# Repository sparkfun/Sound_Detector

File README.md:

#Sound_detector
***

[  
*Sound Detector*](https://www.sparkfun.com/products/12642)  

Electret microphone with multiple outputs.

* First output is the actual audio
* Second output is the amplitude envelope
* Third output is a binary "sound present" indication - high while sound is present, low otherwise.

Design and firmware files for the [VKey Voltage Keypad](https://www.sparkfun.com/products/12080).

Repository Contents
-------------------

* **/Documents** - Additional design files including LTspice simulation  
* **/Hardware** - Eagle PCB and schematic files
* **/Production** - Production panel file
* **/Software** - Arduino example code

License Information
-------------------
The hardware is released under [Creative Commons ShareAlike 4.0 International](https://creativecommons.org/licenses/by-sa/4.0/).
The code is beerware; if you see me (or any other SparkFun employee) at the local, and you've found our code helpful, please buy us a round!

Distributed as-is; no warranty is given.

Author: Byron Jacquot @ SparkFun Electonics

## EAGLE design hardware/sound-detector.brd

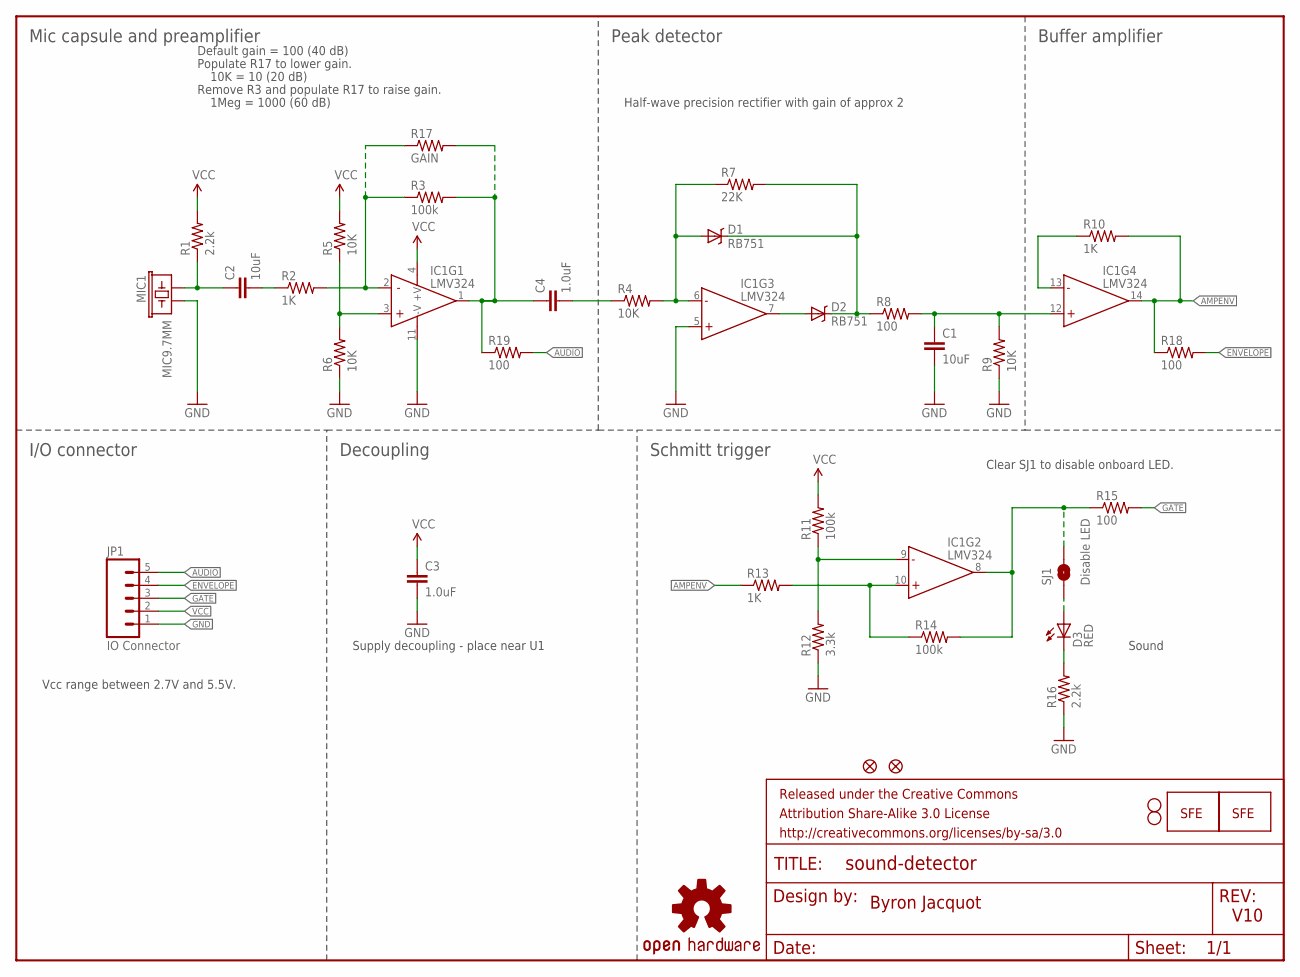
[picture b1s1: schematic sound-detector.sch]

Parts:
C1, C2: 10uF; 1206
C3, C4: 1.0uF; 0603-CAP
D1, D2: RB751; SOD-523
D3: RED; LED-0603
FID3, FID4: FIDUCIAL1X2; FIDUCIAL-1X2
FRAME1: FRAME-LETTER; CREATIVE_COMMONS
IC1: LMV324; SO014
JP1: IO Connector; 1X05
LOGO1: OSHW-LOGOM; OSHW-LOGO-M
LOGO2: LOGO-SFENW2; SFE-NEW-WEB
LOGO3: LOGO-SFESK; SFE-LOGO-FLAME
MIC1: MIC9.7MM; MIC-9.7MM
R1, R16: 2.2k; 0603-RES
R2, R10, R13: 1K; 0603-RES
R3, R11, R14: 100k; 0603-RES
R4, R5, R6, R9: 10K; 0603-RES
R7: 22K; 0603-RES
R8, R15, R18, R19: 100; 0603-RES
R12: 3.3k; 0603-RES
R17: GAIN; AXIAL-0.1EZ
SJ1: Disable LED; SJ_2S
STANDOFF1, STANDOFF2: STAND-OFF

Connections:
AMPENV: IC1.14 (OUT), R10.2, R13.1, R18.1
AUDIO: JP1.5, R19.2
ENVELOPE: JP1.4, R18.2
GATE: JP1.3, R15.2
GND: C1.2, C3.2, IC1.5 (+IN), IC1.11 (-V), JP1.1, MIC1.2, R6.1, R9.1, R12.1, R16.1
N$: C4.1, IC1.1 (OUT), R3.2, R17.P$2 (2), R19.1
unnamed: C2.1, MIC1.1, R1.1
unnamed: IC1.3 (+IN), R5.1, R6.2
unnamed: D3.C, R16.2
unnamed: IC1.2 (-IN), R2.2, R3.1, R17.P$1 (1)
unnamed: C2.2, R2.1
unnamed: C4.2, R4.1
unnamed: D1.A, IC1.6 (-IN), R4.2, R7.1
unnamed: D2.A, IC1.7 (OUT)
unnamed: D1.C, D2.C, R7.2, R8.1
unnamed: C1.1, IC1.12 (+IN), R8.2, R9.2
unnamed: IC1.13 (-IN), R10.1
unnamed: D3.A, SJ1.1
unnamed: IC1.9 (-IN), R11.1, R12.2
unnamed: IC1.10 (+IN), R13.2, R14.1
unnamed: IC1.8 (OUT), R14.2, R15.1, SJ1.2
VCC: C3.1, IC1.4 (+V), JP1.2, R1.2, R5.2, R11.2

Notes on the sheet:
Byron Jacquot
V10
Supply decoupling - place near U1
Mic capsule and preamplifier
Peak detector
Buffer amplifier
I/O connector
Decoupling
Schmitt trigger
Default gain = 100 (40 dB)
Half-wave precision rectifier with gain of approx 2
Vcc range between 2.7V and 5.5V.
Sound
Populate R17 to lower gain.
10K = 10 (20 dB)
Remove R3 and populate R17 to raise gain.
1Meg = 1000 (60 dB)
Clear SJ1 to disable onboard LED.

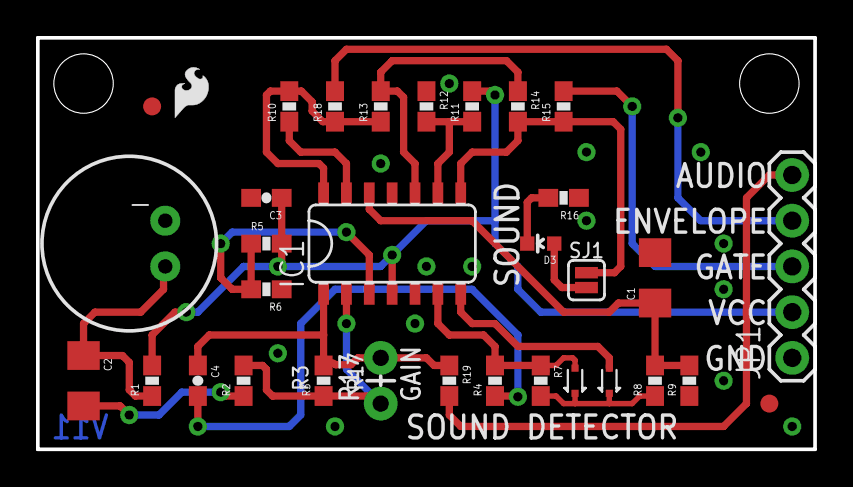
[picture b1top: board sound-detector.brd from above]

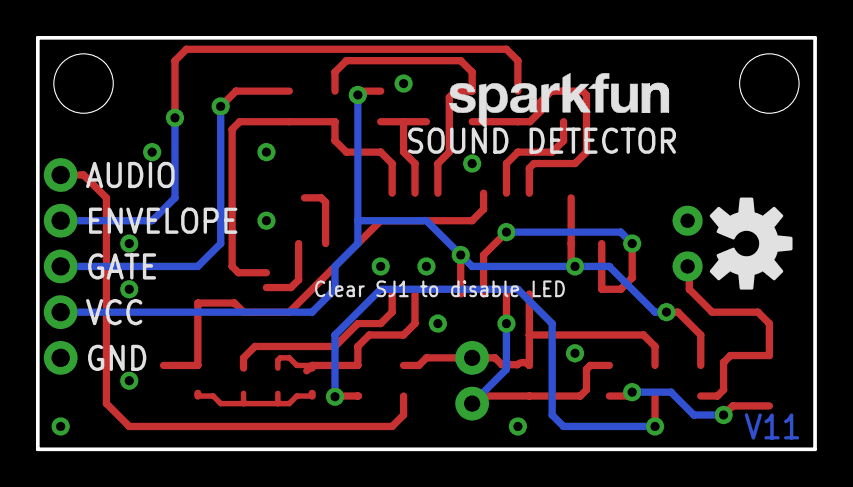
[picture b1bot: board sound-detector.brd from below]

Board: 2 copper layers, 43.2 x 22.9 mm, 38 parts (2 on the bottom side), 22 nets.

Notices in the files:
parts and their libraries:
SparkFun-Aesthetics: Licensing: CC v3.0 Share-Alike You are welcome to use this library for commercial purposes.
SparkFun-Aesthetics: Released under the Creative Commons Attribution Share-Alike 3.0 License
SparkFun-Aesthetics: http://creativecommons.org/licenses/by-sa/3.0
